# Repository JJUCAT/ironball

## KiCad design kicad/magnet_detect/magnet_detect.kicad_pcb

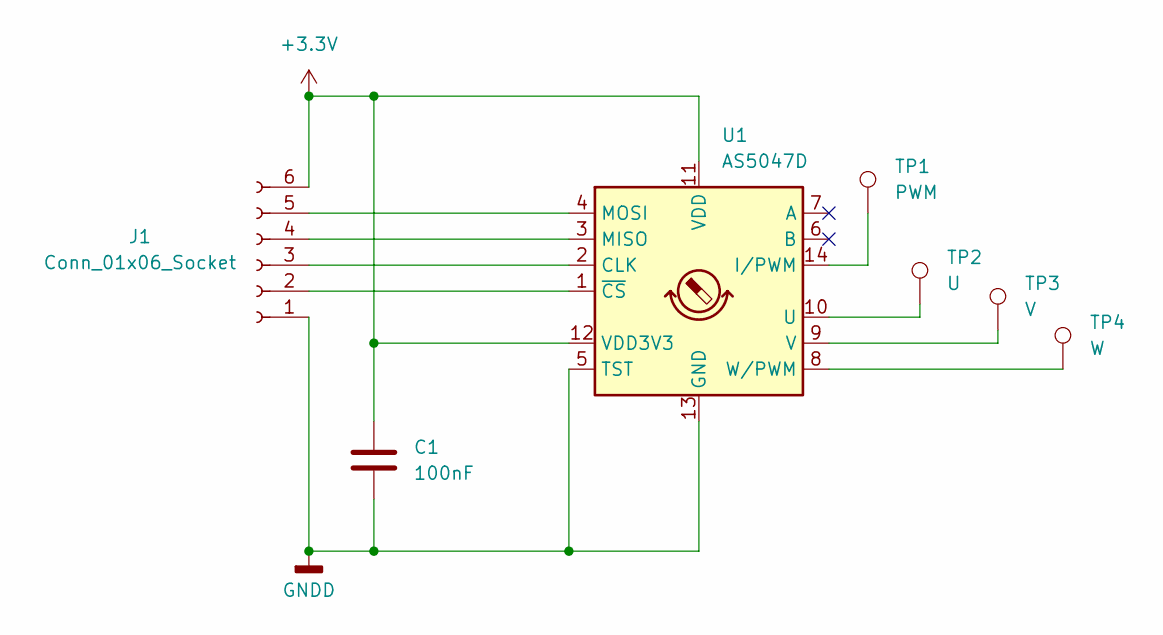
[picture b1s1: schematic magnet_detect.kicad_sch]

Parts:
C1: 100nF; C_0603_1608Metric
J1: Conn_01x06_Socket; JST_PH_S6B-PH-K_1x06_P2.00mm_Horizontal
TP1: PWM; TestPoint_Loop_D1.80mm_Drill1.0mm_Beaded
TP2: U; TestPoint_Loop_D1.80mm_Drill1.0mm_Beaded
TP3: V; TestPoint_Loop_D1.80mm_Drill1.0mm_Beaded
TP4: W; TestPoint_Loop_D1.80mm_Drill1.0mm_Beaded
U1: AS5047D; TSSOP-14_4.4x5mm_P0.65mm

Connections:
+3.3V: C1.1, J1.6, U1.11 (VDD), U1.12 (VDD3V3)
GNDD: C1.2, J1.1, U1.5 (TST), U1.13 (GND)
unnamed: J1.2, U1.1 (~CS)
unnamed: J1.3, U1.2 (CLK)
unnamed: J1.4, U1.3 (MISO)
unnamed: J1.5, U1.4 (MOSI)
unnamed: TP1.1, U1.14 (I/PWM)
unnamed: TP2.1, U1.10 (U)
unnamed: TP3.1, U1.9 (V)
unnamed: TP4.1, U1.8 (W/PWM)

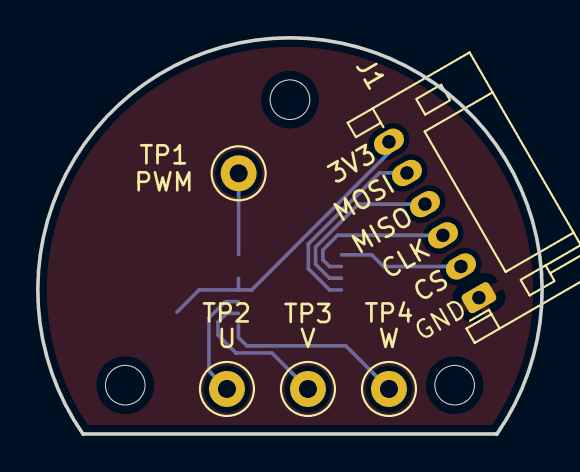
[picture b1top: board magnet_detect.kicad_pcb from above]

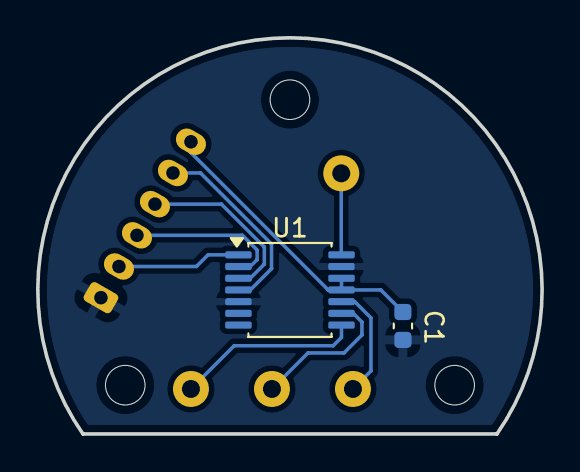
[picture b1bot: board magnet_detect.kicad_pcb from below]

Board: 2 copper layers, 28.0 x 22.0 mm, 7 parts (2 on the bottom side), 10 nets.

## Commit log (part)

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2026-05-24 feat(ironball):架构
2026-05-27 fix(doc):develop board data
2026-05-28 feat(esp32s3):esp32 proj
2026-05-30 fix(managed_components):esp camera components
2026-05-30 fix(components):camera components
2026-05-30 fix(console_cmd_wifi):console wifi
2026-06-02 feat(freecad):2204motor
2026-06-03 fix(freecad):2204motor
2026-06-03 fix(freecad):remove FCBak
2026-06-03 fix(kicad):magnet_detect
2026-06-04 fix(kicad):esp32_magnet
2026-06-04 fix(freecad):torque_hinge
2026-06-06 fix(freecad):esp32s3wroom
2026-06-06 fix(kicad):esp32 base sch
2026-06-10 fix(kicad):esp32
2026-06-10 fix(kicad):as5047p
2026-06-12 fix(kicad):dy-sv17f
2026-06-12 feat(esp_websocket_client):websocket
2026-06-13 feat(component):wifi manager
2026-06-14 fix(wifi_manager):log
2026-06-14 fix(ironball_server):prompt
2026-06-14 fix(wifi_manager):commit
2026-06-16 fix(wifi_manager):some commit
2026-06-19 fix(wifi_manager):config
2026-06-19 fix(wifi_manager):remove dns
